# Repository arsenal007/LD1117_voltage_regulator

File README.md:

<<<<<<< HEAD
 - KiCAD Cproject for simple 1.2..5.0v LD1117 SOT-223 voltage regulator. 
 - PCB layout and schematics 

 - Gerber files </p>
 - FlatCAM CNC files for milling </p>
=======
KiCAD Cproject for simple 1.2..5.0v LD1117 SOT-223 voltage regulator. 
PCB layout and schematics 

<p> Gerber files </p>
<p> FlatCAM CNC files for milling </p>
>>>>>>> 4be874f02be512fb7f5c20e92b526005ecc44e2b

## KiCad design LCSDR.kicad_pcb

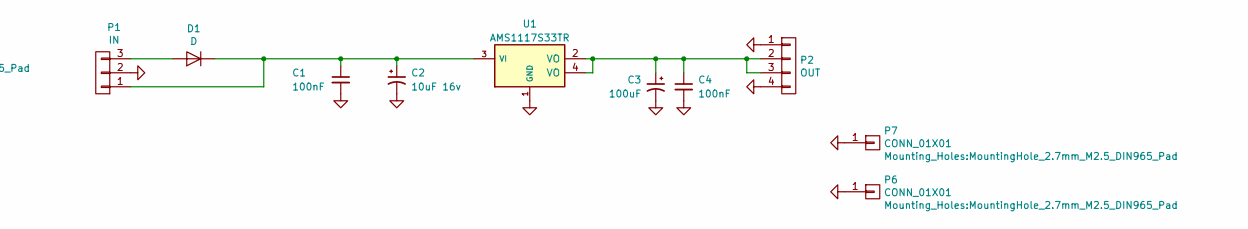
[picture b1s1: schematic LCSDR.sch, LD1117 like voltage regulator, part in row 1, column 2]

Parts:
C1, C4: 100nF; C_1206_0603
C2: 10uF 16v; Universal_C_Radial_D5_L11_P2_tantal
C3: 100uF; CP_Radial_D6.3mm_P2.50mm
D1: D; D_DO-41_SOD81_P12.70mm_Horizontal
P1: IN; Pin_Header_Straight_1x03_Pitch2.54mm
P2: OUT; Pin_Header_Straight_1x04_Pitch2.54mm
P5, P6, P7: CONN_01X01; MountingHole_2.7mm_M2.5_DIN965_Pad
U1: AMS1117S33TR; SOT-223

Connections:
GND: C1.2, C2.2, C3.2, C4.2, P1.2, P2.1, P2.4, P5.1, P6.1, P7.1, U1.1 (GND)
unnamed: C1.1, C2.1, D1.1 (K), P1.1, U1.3 (VI)
unnamed: C3.1, C4.1, P2.2, P2.3, U1.2 (VO), U1.4 (VO)
unnamed: D1.2 (A), P1.3

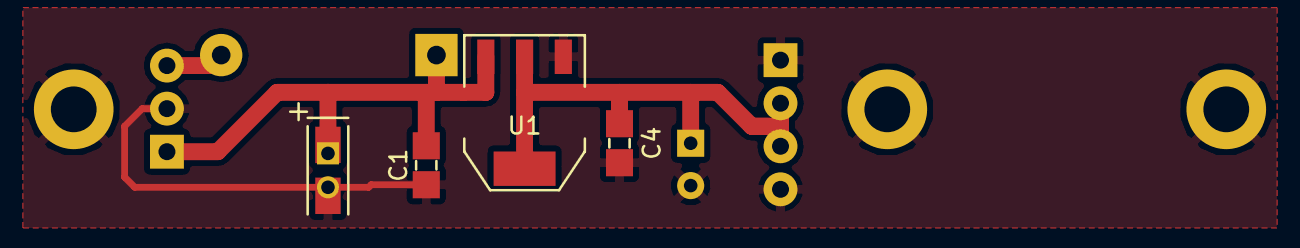
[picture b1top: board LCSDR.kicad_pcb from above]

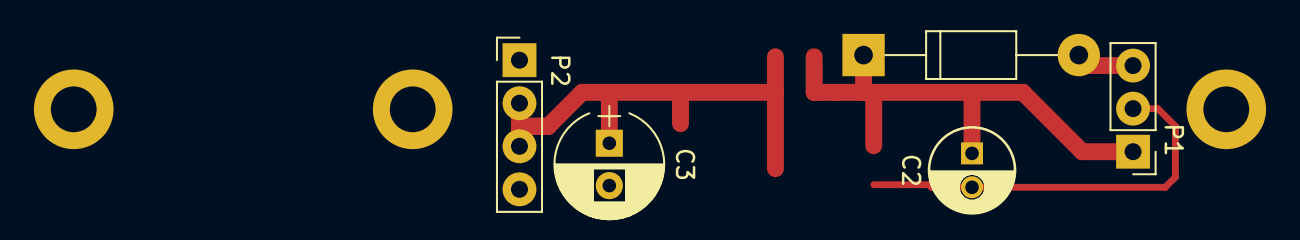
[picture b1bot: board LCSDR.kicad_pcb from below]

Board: 2 copper layers, 11 parts (5 on the bottom side), 4 nets.

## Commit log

2017-12-06 initial project version
2017-12-06 Fix all indexes
2017-12-06 version with USB cable 3mm
2017-12-10 Relese version PCB with CNC files
2017-12-10 Add schematics image and PCB 3D
2017-12-10 correcting Images in README
2017-12-10 README
